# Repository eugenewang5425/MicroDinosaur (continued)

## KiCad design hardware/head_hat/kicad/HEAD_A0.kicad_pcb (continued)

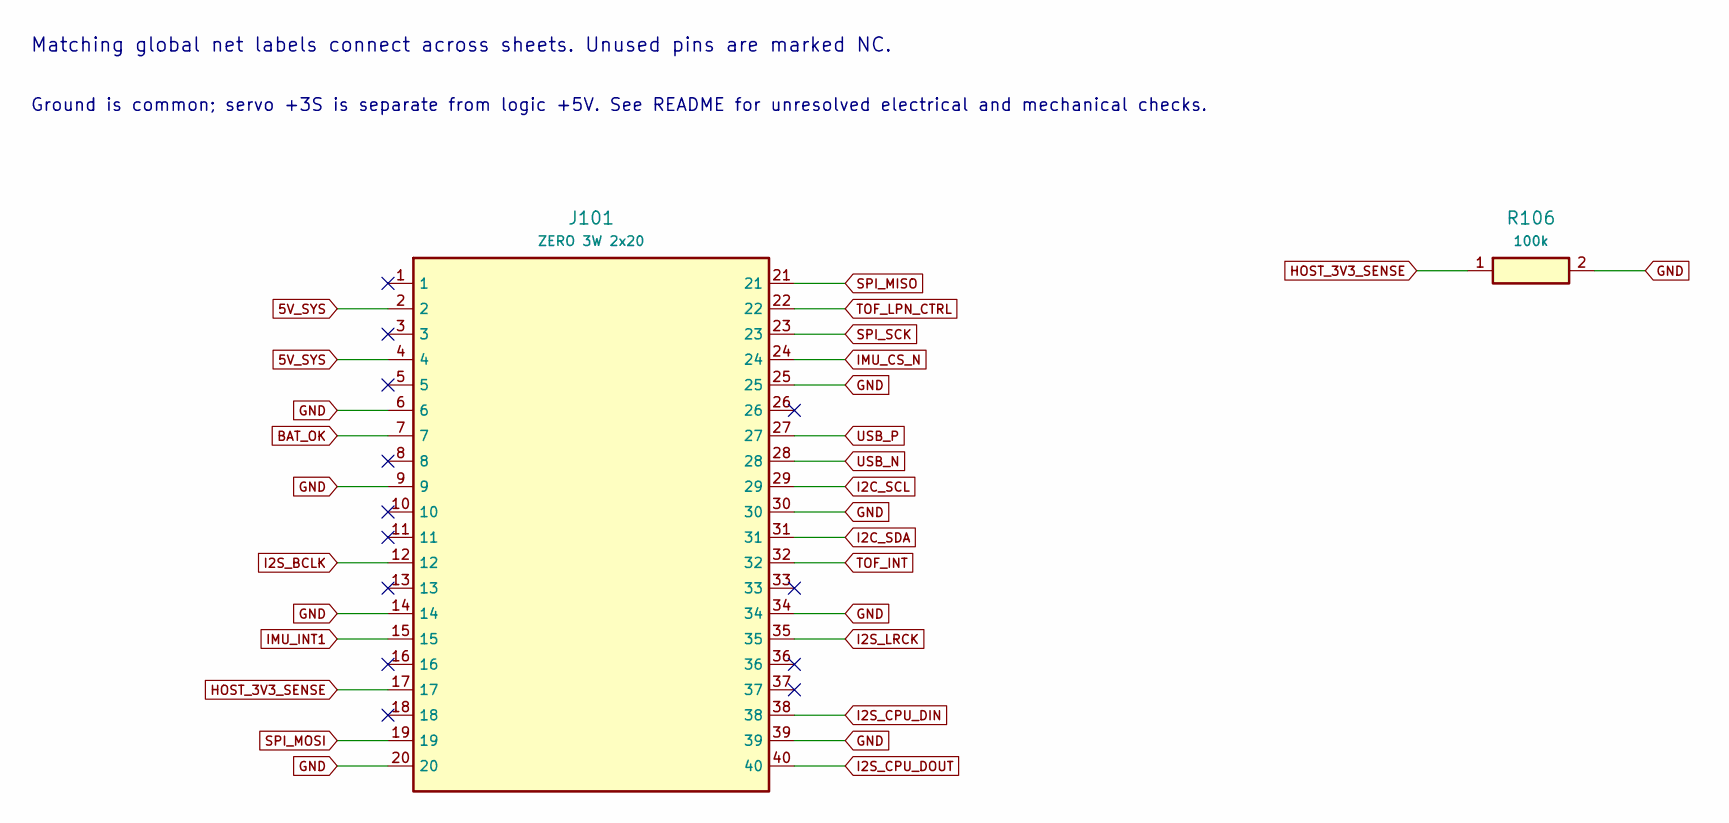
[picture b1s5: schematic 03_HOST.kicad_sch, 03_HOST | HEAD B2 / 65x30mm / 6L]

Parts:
J101: ZERO 3W 2x20; Connector_PinHeader_2.54mm__PinHeader_2x20_P2.54mm_Vertical; MPN 61304021121
R106: 100k; Resistor_SMD__R_0402_1005Metric; MPN RC0402FR-07100KL

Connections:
5V_SYS: J101.2, J101.4; also elsewhere on the board
BAT_OK: J101.7; also elsewhere on the board
GND: J101.6, J101.9, J101.14, J101.20, J101.25, J101.30, J101.34, J101.39, R106.2; also elsewhere on the board
HOST_3V3_SENSE: J101.17, R106.1; also elsewhere on the board
I2C_SCL: J101.29; also elsewhere on the board
I2C_SDA: J101.31; also elsewhere on the board
I2S_BCLK: J101.12; also elsewhere on the board
I2S_CPU_DIN: J101.38; also elsewhere on the board
I2S_CPU_DOUT: J101.40; also elsewhere on the board
I2S_LRCK: J101.35; also elsewhere on the board
IMU_CS_N: J101.24; also elsewhere on the board
IMU_INT1: J101.15; also elsewhere on the board
SPI_MISO: J101.21; also elsewhere on the board
SPI_MOSI: J101.19; also elsewhere on the board
SPI_SCK: J101.23; also elsewhere on the board
TOF_INT: J101.32; also elsewhere on the board
TOF_LPN_CTRL: J101.22; also elsewhere on the board
USB_N: J101.28; also elsewhere on the board
USB_P: J101.27; also elsewhere on the board

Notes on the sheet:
Matching global net labels connect across sheets. Unused pins are marked NC.
Ground is common; servo +3S is separate from logic +5V. See README for unresolved electrical and mechanical checks.

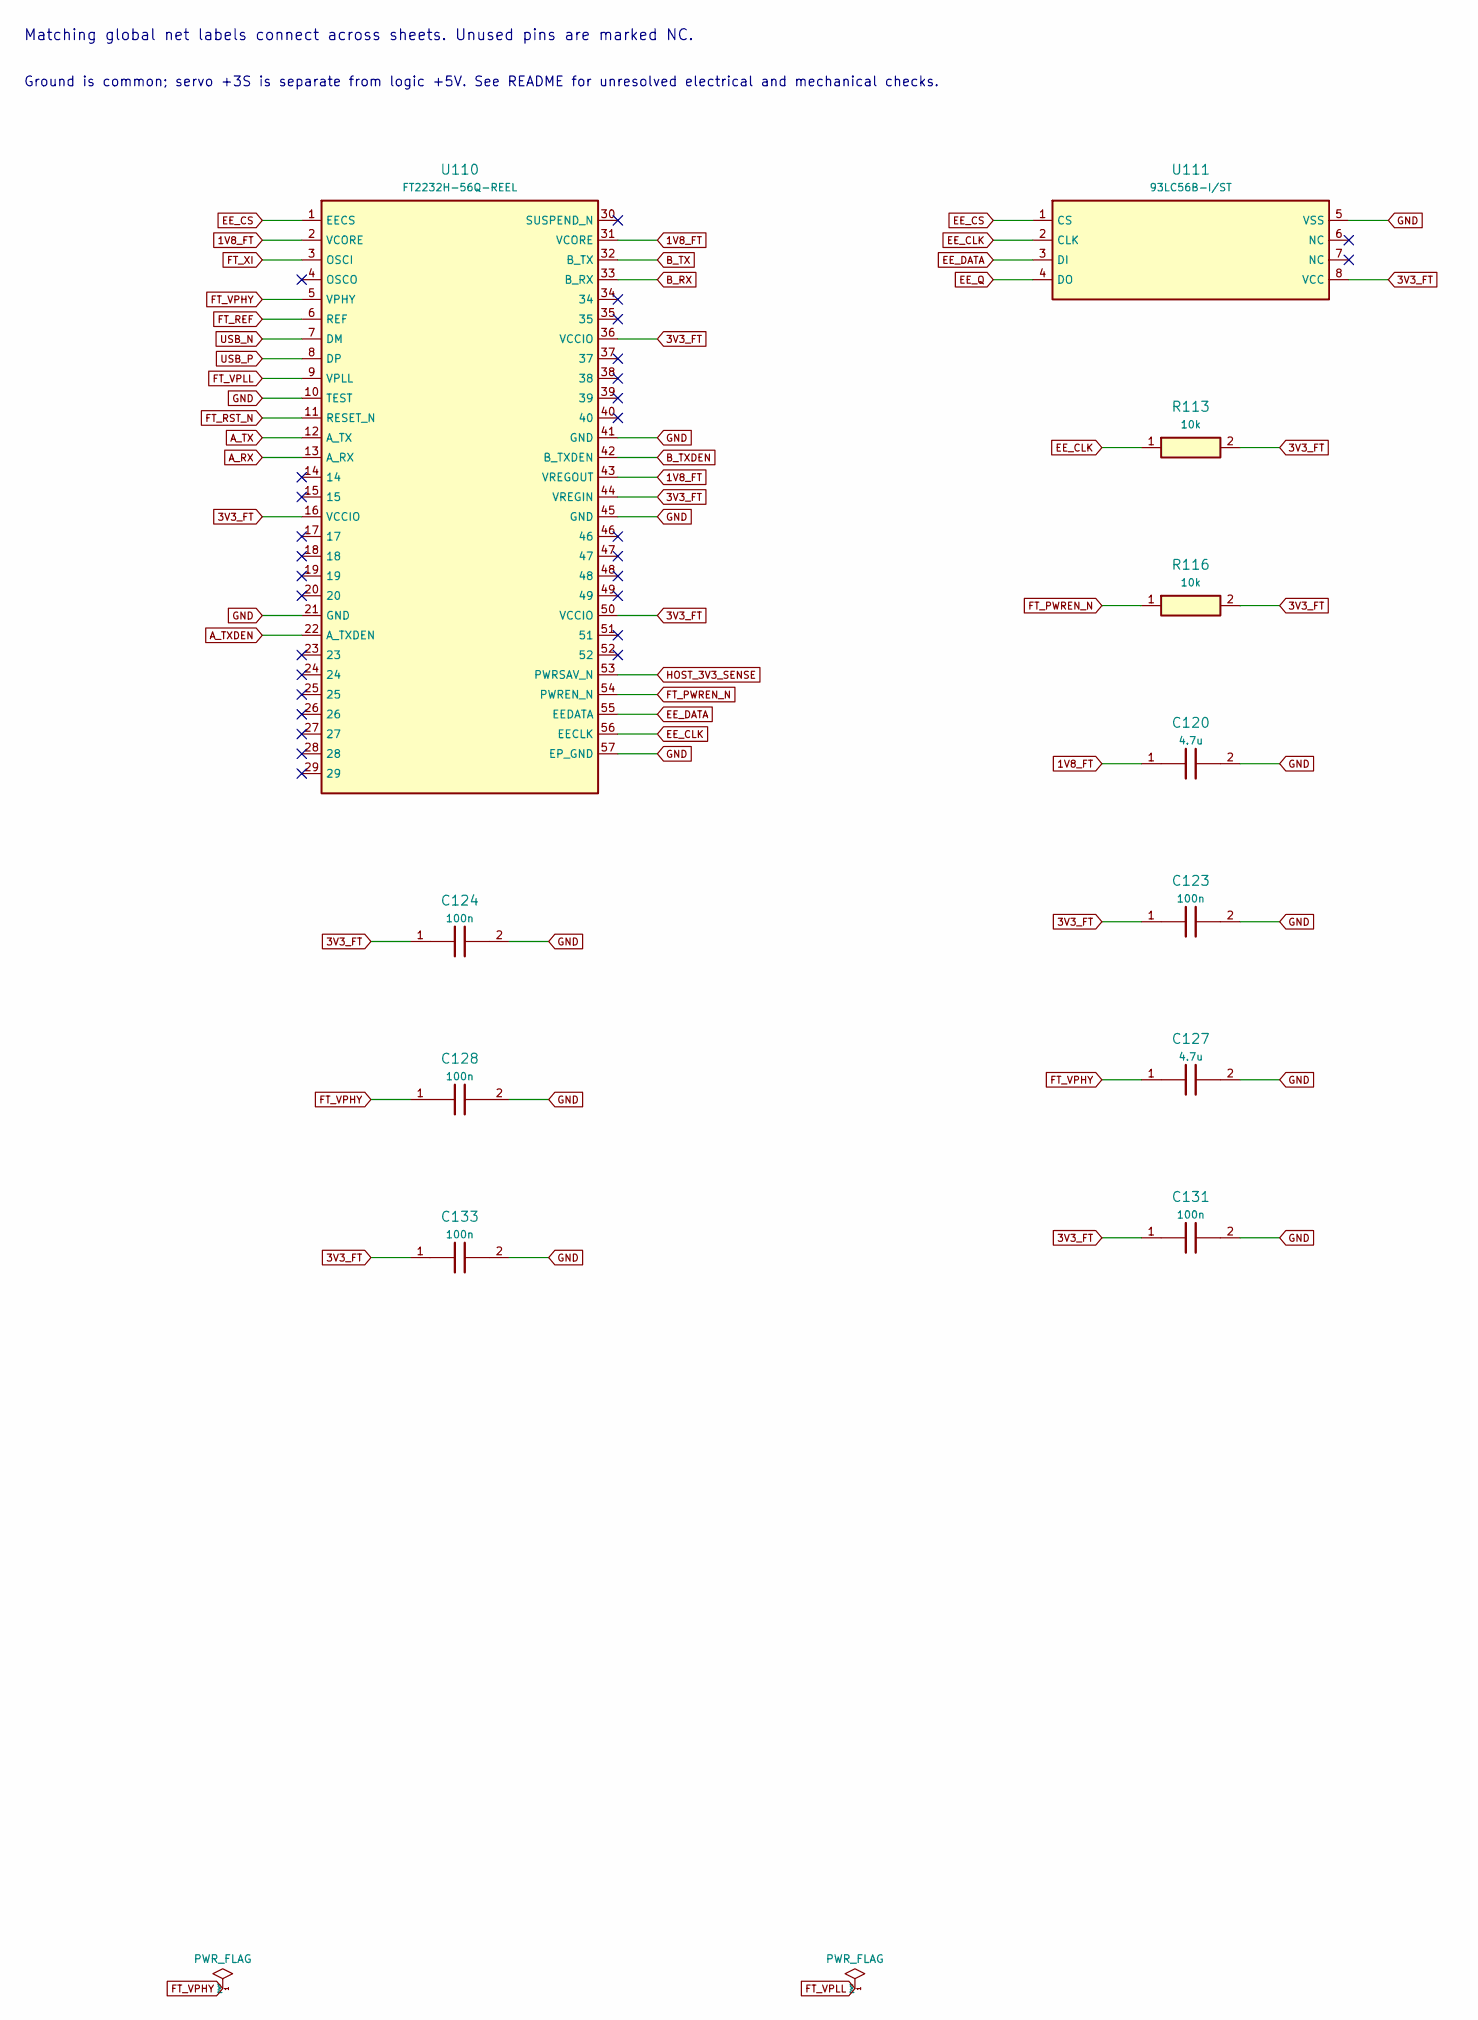
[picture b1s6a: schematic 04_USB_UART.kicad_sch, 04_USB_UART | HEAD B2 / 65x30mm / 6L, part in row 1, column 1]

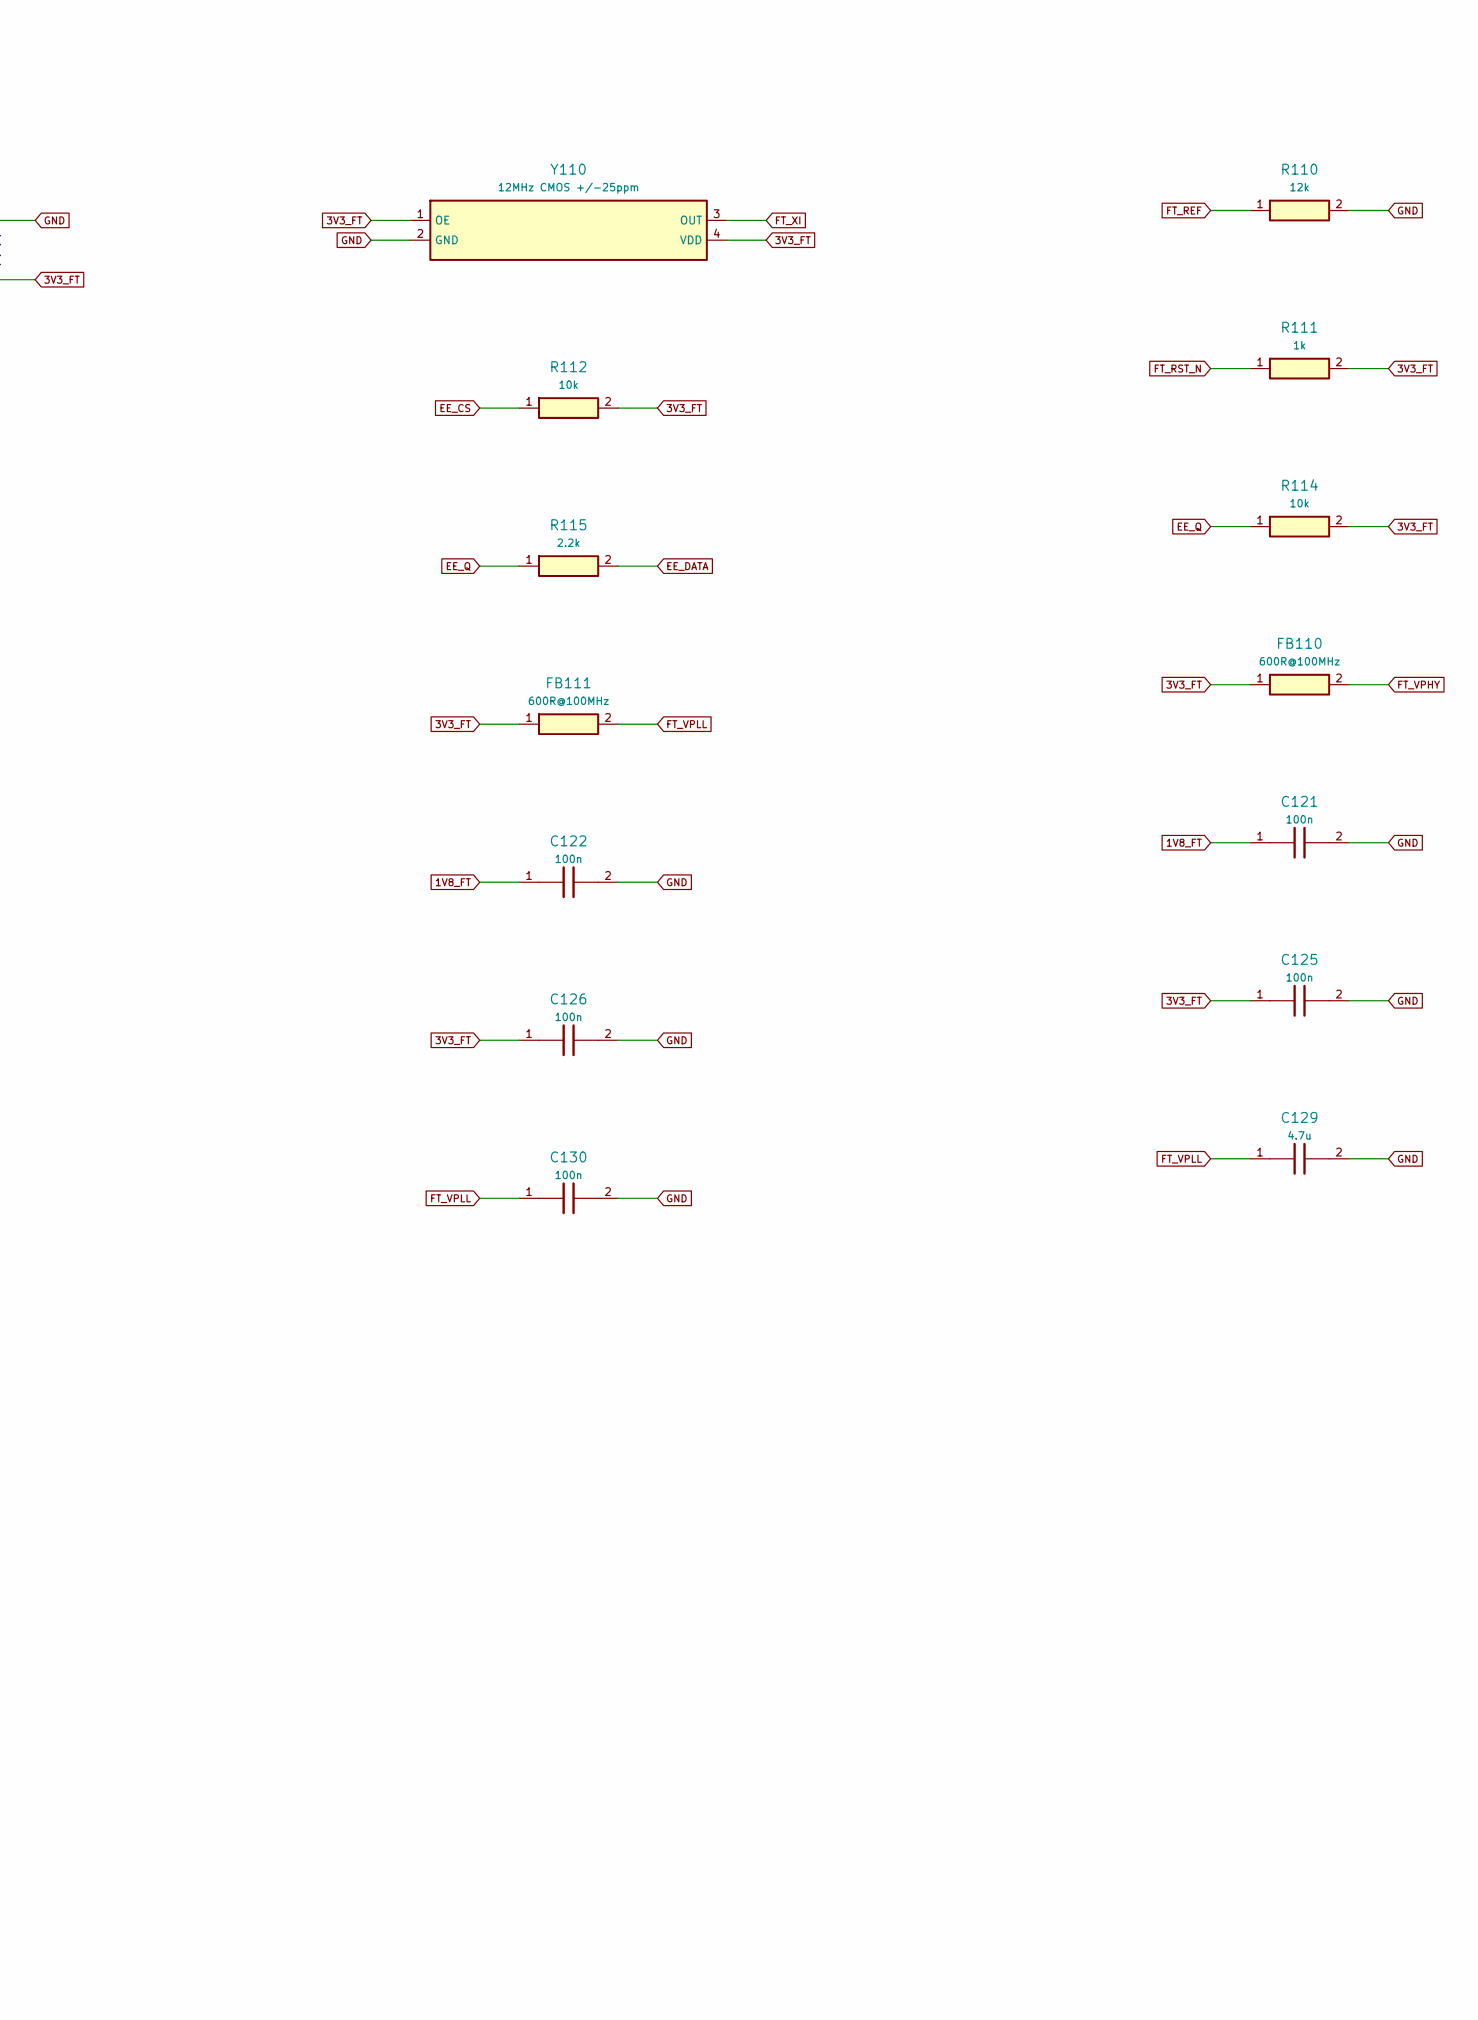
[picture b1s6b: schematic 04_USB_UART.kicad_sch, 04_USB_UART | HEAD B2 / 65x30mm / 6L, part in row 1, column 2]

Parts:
C120, C127, C129: 4.7u; Capacitor_SMD__C_0603_1608Metric; MPN GRM188R60J475KE19D
C121, C122, C123, C124, C125, C126, C128, C130, C131, C133: 100n; Capacitor_SMD__C_0402_1005Metric; MPN GRM155R71C104KA88D
FB110, FB111: 600R@100MHz; Resistor_SMD__R_0603_1608Metric; MPN BLM18AG601SN1D
R110: 12k; Resistor_SMD__R_0402_1005Metric; MPN RC0402FR-0712KL
R111: 1k; Resistor_SMD__R_0402_1005Metric; MPN RC0402FR-071KL
R112, R113, R114, R116: 10k; Resistor_SMD__R_0402_1005Metric; MPN RC0402FR-0710KL
R115: 2.2k; Resistor_SMD__R_0402_1005Metric; MPN RC0402FR-072K2L
U110: FT2232H-56Q-REEL; Package_DFN_QFN__QFN-56-1EP_8x8mm_P0.5mm_EP5.9x5.9mm; MPN FT2232H-56Q-REEL
U111: 93LC56B-I/ST; Package_SO__TSSOP-8_3x3mm_P0.65mm; MPN 93LC56B-I/ST
Y110: 12MHz CMOS +/-25ppm; SiTime_2520_Oscillator; MPN SiT1602BI-12-33E-12.000000E

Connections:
1V8_FT: C120.1, C121.1, C122.1, U110.2 (VCORE), U110.31 (VCORE), U110.43 (VREGOUT)
3V3_FT: C123.1, C124.1, C125.1, C126.1, C131.1, C133.1, FB110.1, FB111.1, R111.2, R112.2, R113.2, R114.2, R116.2, U110.16 (VCCIO), U110.36 (VCCIO), U110.44 (VREGIN), U110.50 (VCCIO), U111.8 (VCC), Y110.1 (OE), Y110.4 (VDD); also elsewhere on the board
A_RX: U110.13 (A_RX); also elsewhere on the board
A_TX: U110.12 (A_TX); also elsewhere on the board
A_TXDEN: U110.22 (A_TXDEN); also elsewhere on the board
B_RX: U110.33 (B_RX); also elsewhere on the board
B_TX: U110.32 (B_TX); also elsewhere on the board
B_TXDEN: U110.42 (B_TXDEN); also elsewhere on the board
EE_CLK: R113.1, U110.56 (EECLK), U111.2 (CLK)
EE_CS: R112.1, U110.1 (EECS), U111.1 (CS)
EE_DATA: R115.2, U110.55 (EEDATA), U111.3 (DI)
EE_Q: R114.1, R115.1, U111.4 (DO)
FT_PWREN_N: R116.1, U110.54 (PWREN_N); also elsewhere on the board
FT_REF: R110.1, U110.6 (REF)
FT_RST_N: R111.1, U110.11 (RESET_N)
FT_VPHY: C127.1, C128.1, FB110.2, U110.5 (VPHY)
FT_VPLL: C129.1, C130.1, FB111.2, U110.9 (VPLL)
FT_XI: U110.3 (OSCI), Y110.3 (OUT)
GND: C120.2, C121.2, C122.2, C123.2, C124.2, C125.2, C126.2, C127.2, C128.2, C129.2, C130.2, C131.2, C133.2, R110.2, U110.10 (TEST), U110.21 (GND), U110.41 (GND), U110.45 (GND), U110.57 (EP_GND), U111.5 (VSS), Y110.2 (GND); also elsewhere on the board
HOST_3V3_SENSE: U110.53 (PWRSAV_N); also elsewhere on the board
USB_N: U110.7 (DM); also elsewhere on the board
USB_P: U110.8 (DP); also elsewhere on the board

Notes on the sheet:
Matching global net labels connect across sheets. Unused pins are marked NC.
Ground is common; servo +3S is separate from logic +5V. See README for unresolved electrical and mechanical checks.

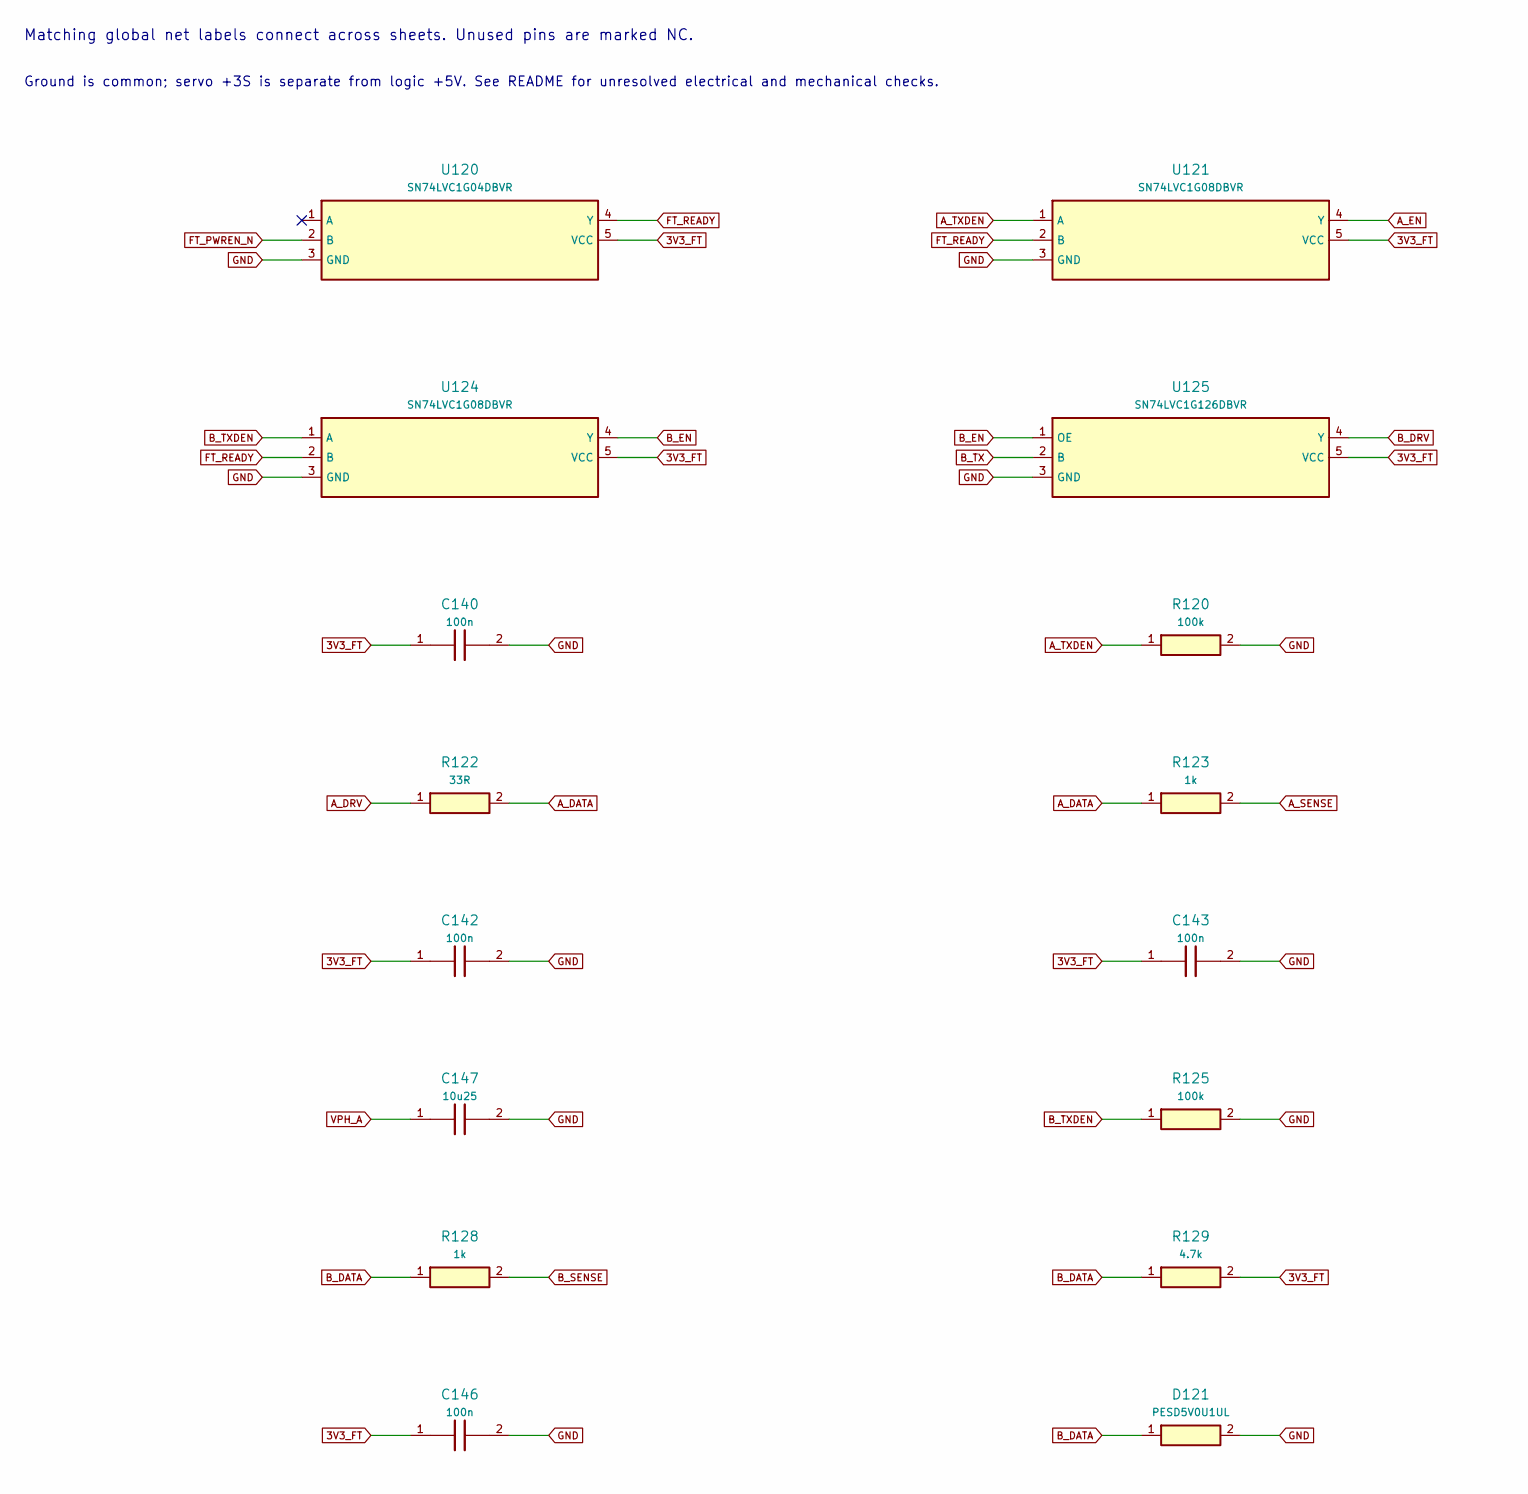
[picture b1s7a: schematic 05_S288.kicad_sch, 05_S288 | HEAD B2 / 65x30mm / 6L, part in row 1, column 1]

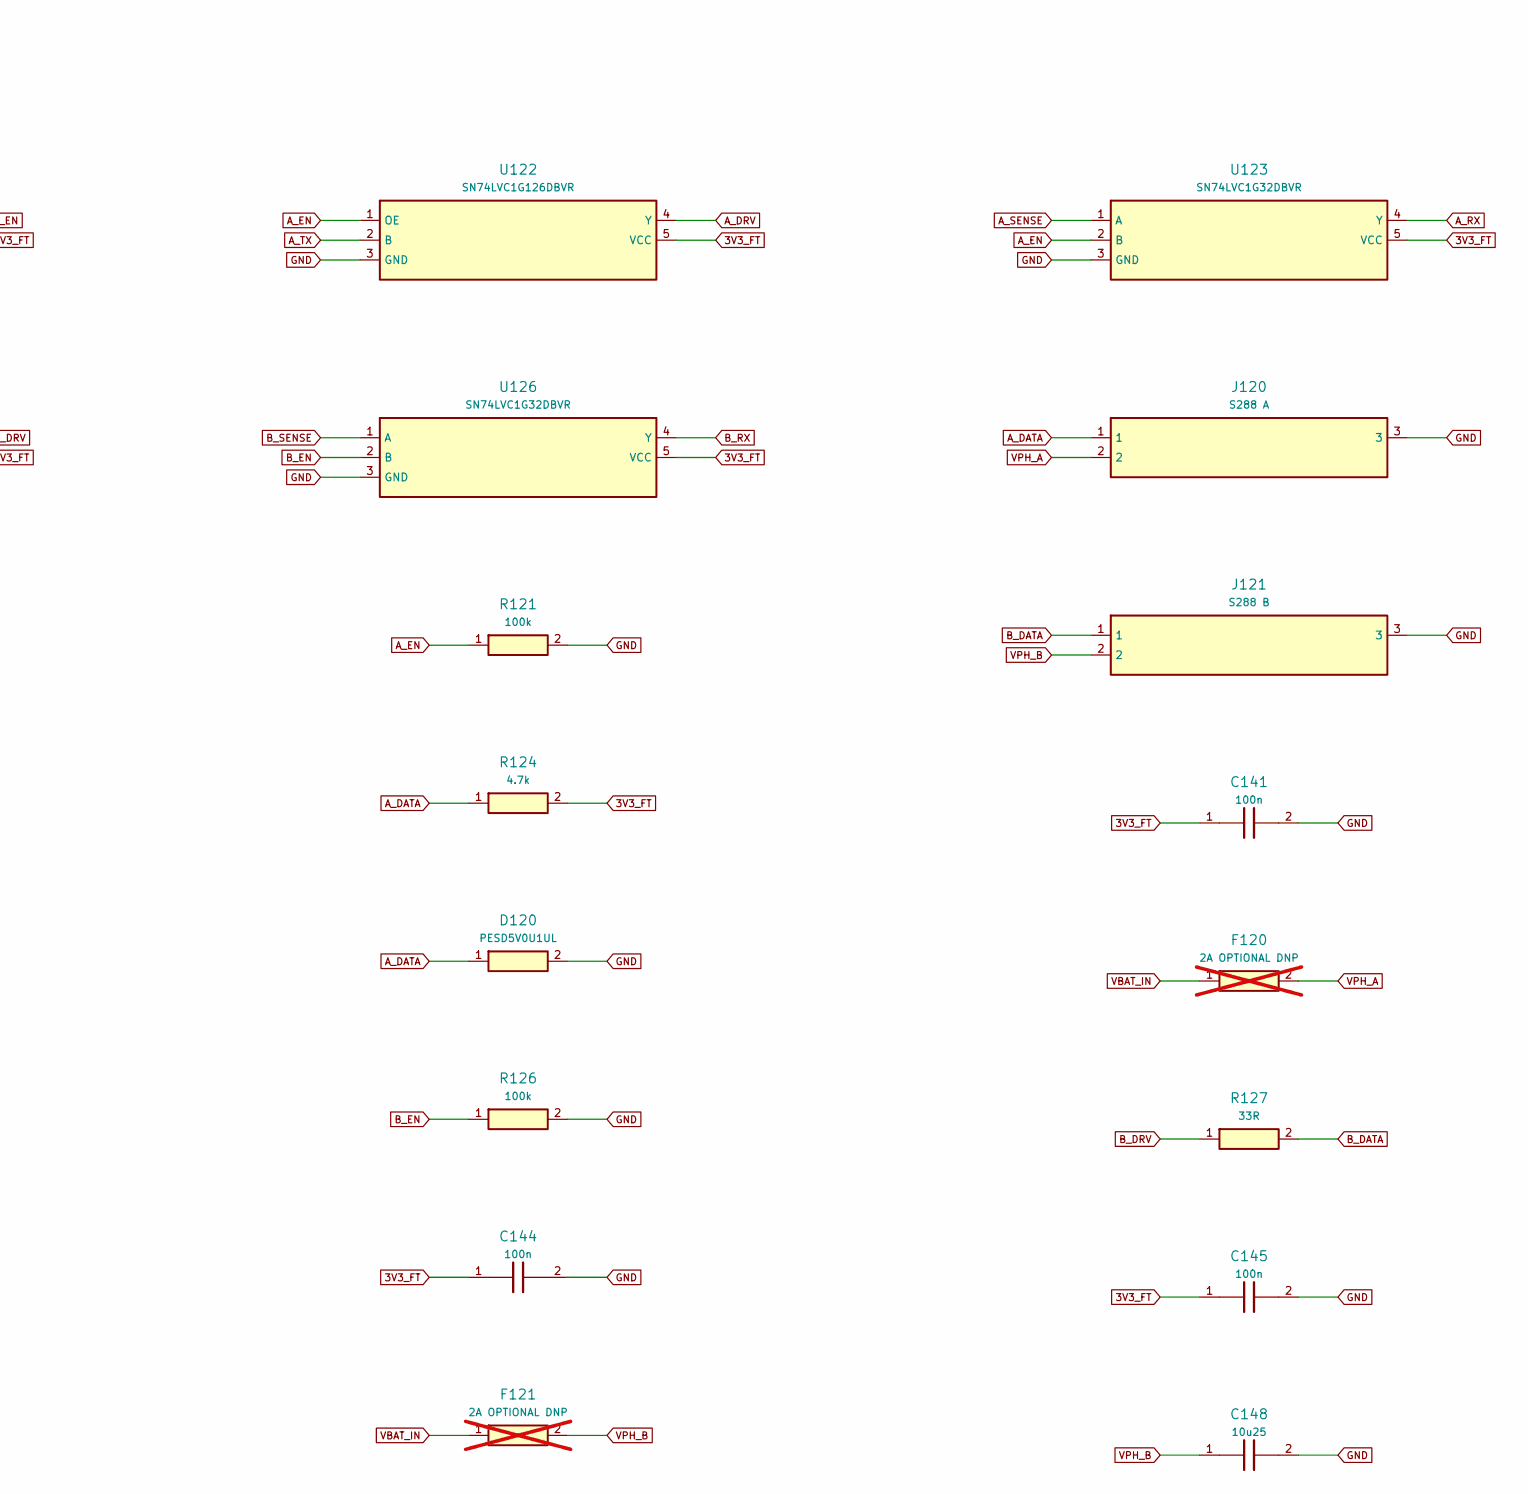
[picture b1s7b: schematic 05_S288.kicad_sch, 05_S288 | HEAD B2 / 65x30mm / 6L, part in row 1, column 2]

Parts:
C140, C141, C142, C143, C144, C145, C146: 100n; Capacitor_SMD__C_0402_1005Metric; MPN GRM155R71C104KA88D
C147, C148: 10u25; Capacitor_SMD__C_1206_3216Metric; MPN GRM31CR71E106KA12L
D120, D121: PESD5V0U1UL; Diode_SMD__D_SOD-882; MPN PESD5V0U1UL,315
F120, F121: 2A OPTIONAL DNP; Fuse__Fuse_1206_3216Metric; MPN 0467002.NR; not fitted
J120: S288 A; Connector_JST__JST_PH_B3B-PH-K_1x03_P2.00mm_Vertical; MPN B3B-PH-K-S
J121: S288 B; Connector_JST__JST_PH_B3B-PH-K_1x03_P2.00mm_Vertical; MPN B3B-PH-K-S
R120, R121, R125, R126: 100k; Resistor_SMD__R_0402_1005Metric; MPN RC0402FR-07100KL
R122, R127: 33R; Resistor_SMD__R_0402_1005Metric; MPN RC0402FR-0733RL
R123, R128: 1k; Resistor_SMD__R_0402_1005Metric; MPN RC0402FR-071KL
R124, R129: 4.7k; Resistor_SMD__R_0402_1005Metric; MPN RC0402FR-074K7L
U120: SN74LVC1G04DBVR; Package_TO_SOT_SMD__SOT-23-5; MPN SN74LVC1G04DBVR
U121, U124: SN74LVC1G08DBVR; Package_TO_SOT_SMD__SOT-23-5; MPN SN74LVC1G08DBVR
U122, U125: SN74LVC1G126DBVR; Package_TO_SOT_SMD__SOT-23-5; MPN SN74LVC1G126DBVR
U123, U126: SN74LVC1G32DBVR; Package_TO_SOT_SMD__SOT-23-5; MPN SN74LVC1G32DBVR

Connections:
3V3_FT: C140.1, C141.1, C142.1, C143.1, C144.1, C145.1, C146.1, R124.2, R129.2, U120.5 (VCC), U121.5 (VCC), U122.5 (VCC), U123.5 (VCC), U124.5 (VCC), U125.5 (VCC), U126.5 (VCC); also elsewhere on the board
A_DATA: D120.1, J120.1, R122.2, R123.1, R124.1
A_DRV: R122.1, U122.4 (Y)
A_EN: R121.1, U121.4 (Y), U122.1 (OE), U123.2 (B)
A_RX: U123.4 (Y); also elsewhere on the board
A_SENSE: R123.2, U123.1 (A)
A_TX: U122.2 (B); also elsewhere on the board
A_TXDEN: R120.1, U121.1 (A); also elsewhere on the board
B_DATA: D121.1, J121.1, R127.2, R128.1, R129.1
B_DRV: R127.1, U125.4 (Y)
B_EN: R126.1, U124.4 (Y), U125.1 (OE), U126.2 (B)
B_RX: U126.4 (Y); also elsewhere on the board
B_SENSE: R128.2, U126.1 (A)
B_TX: U125.2 (B); also elsewhere on the board
B_TXDEN: R125.1, U124.1 (A); also elsewhere on the board
FT_PWREN_N: U120.2 (B); also elsewhere on the board
FT_READY: U120.4 (Y), U121.2 (B), U124.2 (B)
GND: C140.2, C141.2, C142.2, C143.2, C144.2, C145.2, C146.2, C147.2, C148.2, D120.2, D121.2, J120.3, J121.3, R120.2, R121.2, R125.2, R126.2, U120.3 (GND), U121.3 (GND), U122.3 (GND), U123.3 (GND), U124.3 (GND), U125.3 (GND), U126.3 (GND); also elsewhere on the board
VBAT_IN: F120.1, F121.1; also elsewhere on the board
VPH_A: C147.1, F120.2, J120.2
VPH_B: C148.1, F121.2, J121.2

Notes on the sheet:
Matching global net labels connect across sheets. Unused pins are marked NC.
Ground is common; servo +3S is separate from logic +5V. See README for unresolved electrical and mechanical checks.
